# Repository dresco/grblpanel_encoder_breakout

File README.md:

# Bourns PEC11R encoder breakout

A small breakout PCB for Bourns PEC11R series rotary encoders, using JST PH headers.

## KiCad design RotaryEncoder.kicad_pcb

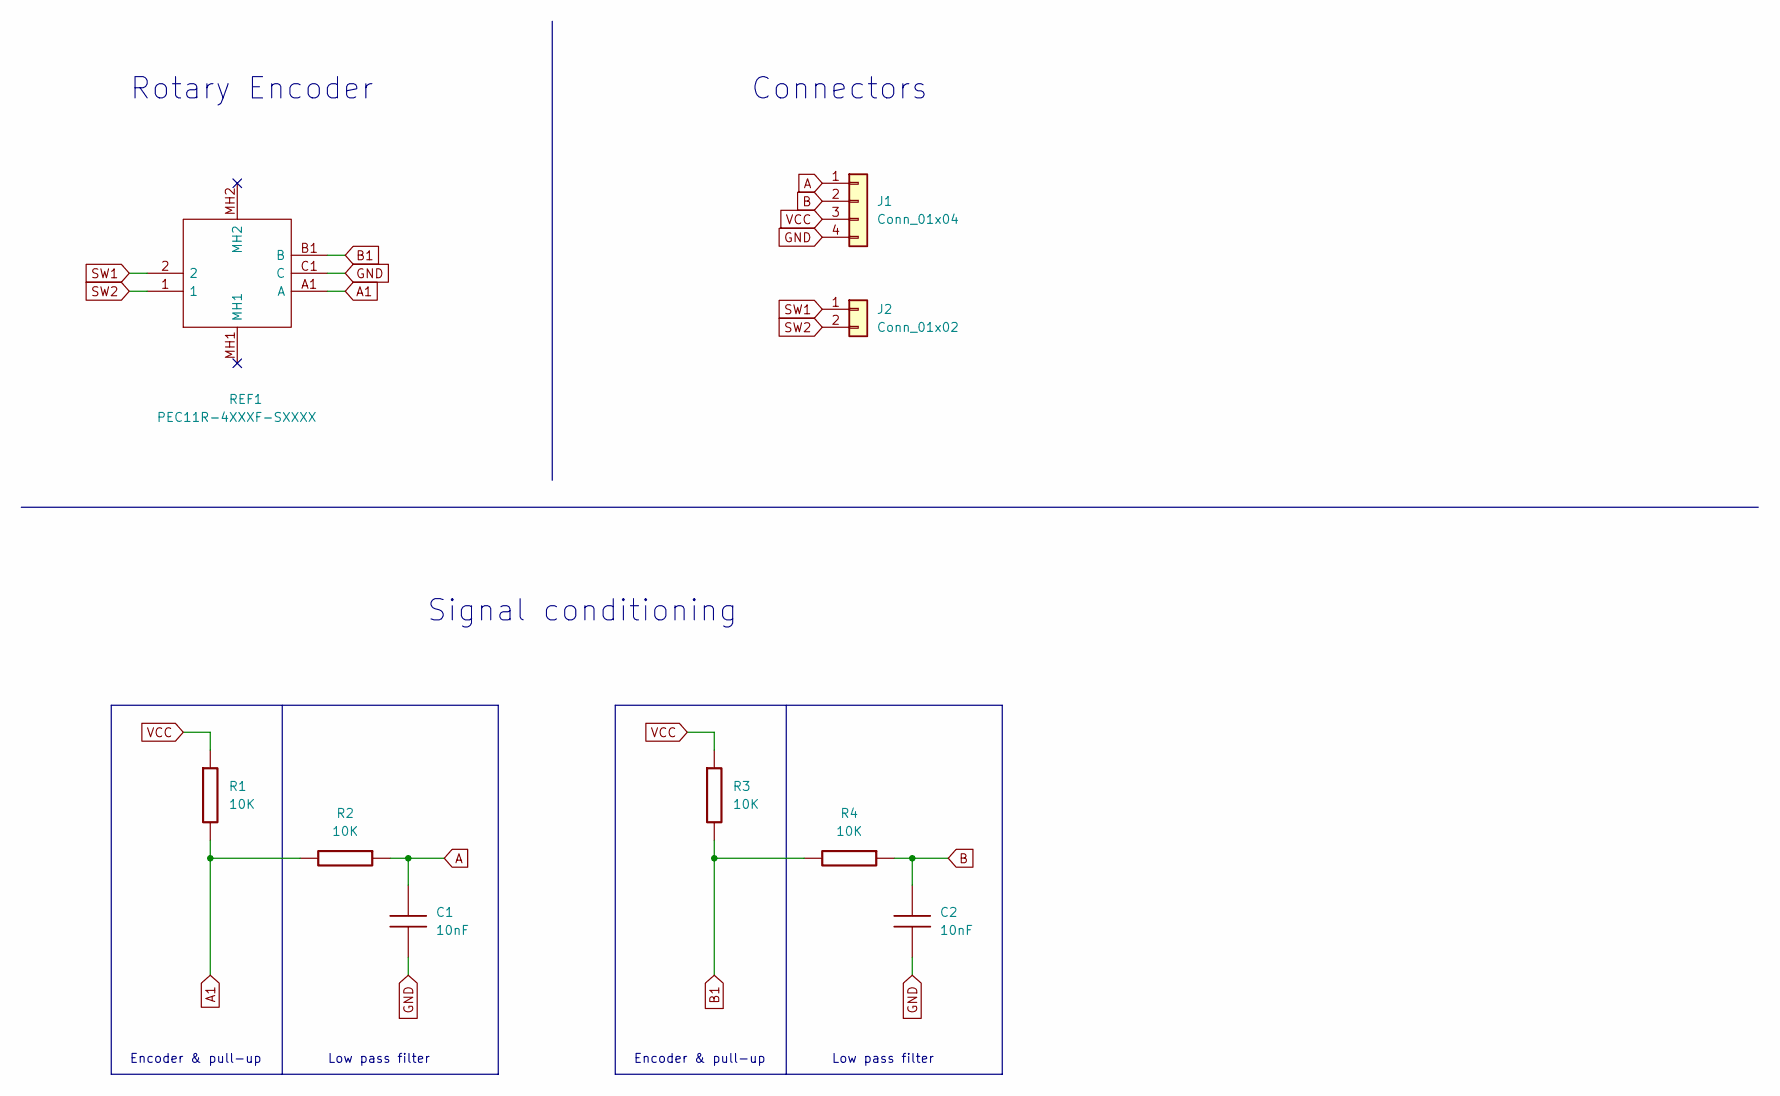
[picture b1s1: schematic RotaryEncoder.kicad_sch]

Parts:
C1, C2: 10nF; C_0603_1608Metric
J1: Conn_01x04; JST_PH_B4B-PH-K_1x04_P2.00mm_Vertical
J2: Conn_01x02; JST_PH_B2B-PH-K_1x02_P2.00mm_Vertical
R1, R2, R3, R4: 10K; R_0603_1608Metric
REF1: PEC11R-4XXXF-SXXXX

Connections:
A: C1.1, J1.1, R2.1
A1: R1.2, R2.2, REF1.A1 (A)
B: C2.1, J1.2, R4.1
B1: R3.2, R4.2, REF1.B1 (B)
GND: C1.2, C2.2, J1.4, REF1.C1 (C)
SW1: J2.1, REF1.2
SW2: J2.2, REF1.1
VCC: J1.3, R1.1, R3.1

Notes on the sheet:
Encoder & pull-up
Rotary Encoder
Low pass filter
Signal conditioning
Connectors

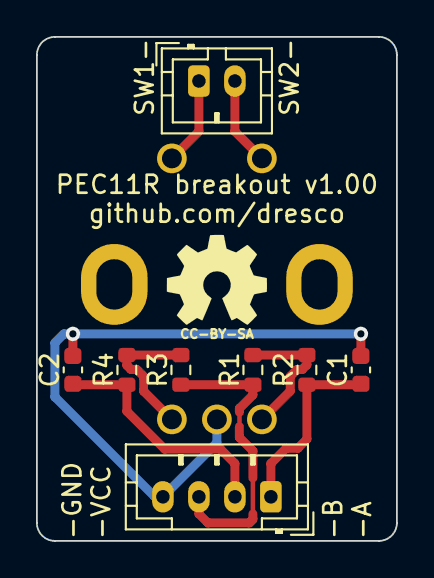
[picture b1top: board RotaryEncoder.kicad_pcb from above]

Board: 2 copper layers, 20.0 x 28.0 mm, 9 parts (1 on the bottom side), 8 nets.

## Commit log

2022-01-05 Initial commit
    Breakout for panel mount Bourns PEC11R rotary encoder with JST PH headers
2022-01-05 Changed encoder mounting holes to oval
2023-06-06 Add manufacturing data
2023-06-10 PCB saved under KiCad v7
    Added README.
    Updated 3d model for encoder.

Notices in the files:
RotaryEncoder.kicad_pcb:
CC-BY-SA
